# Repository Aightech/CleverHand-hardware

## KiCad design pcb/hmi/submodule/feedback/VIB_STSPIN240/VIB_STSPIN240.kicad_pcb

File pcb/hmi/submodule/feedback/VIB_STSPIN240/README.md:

# Vibrotactile STSPIN240 Module
This module is a vibrotactile module that embeds the STSPIN240 motor driver. It is responsible for generating the vibrotactile signals that will be sent to the vibrotactile actuators.

## Electrical Schematic

## PCB Layout
|top view|side view|
|---|---|
|  |  |

## 3D Model
[VIB_STSPIN240_3D](plots/VIB_STSPIN240_pcb.stl)

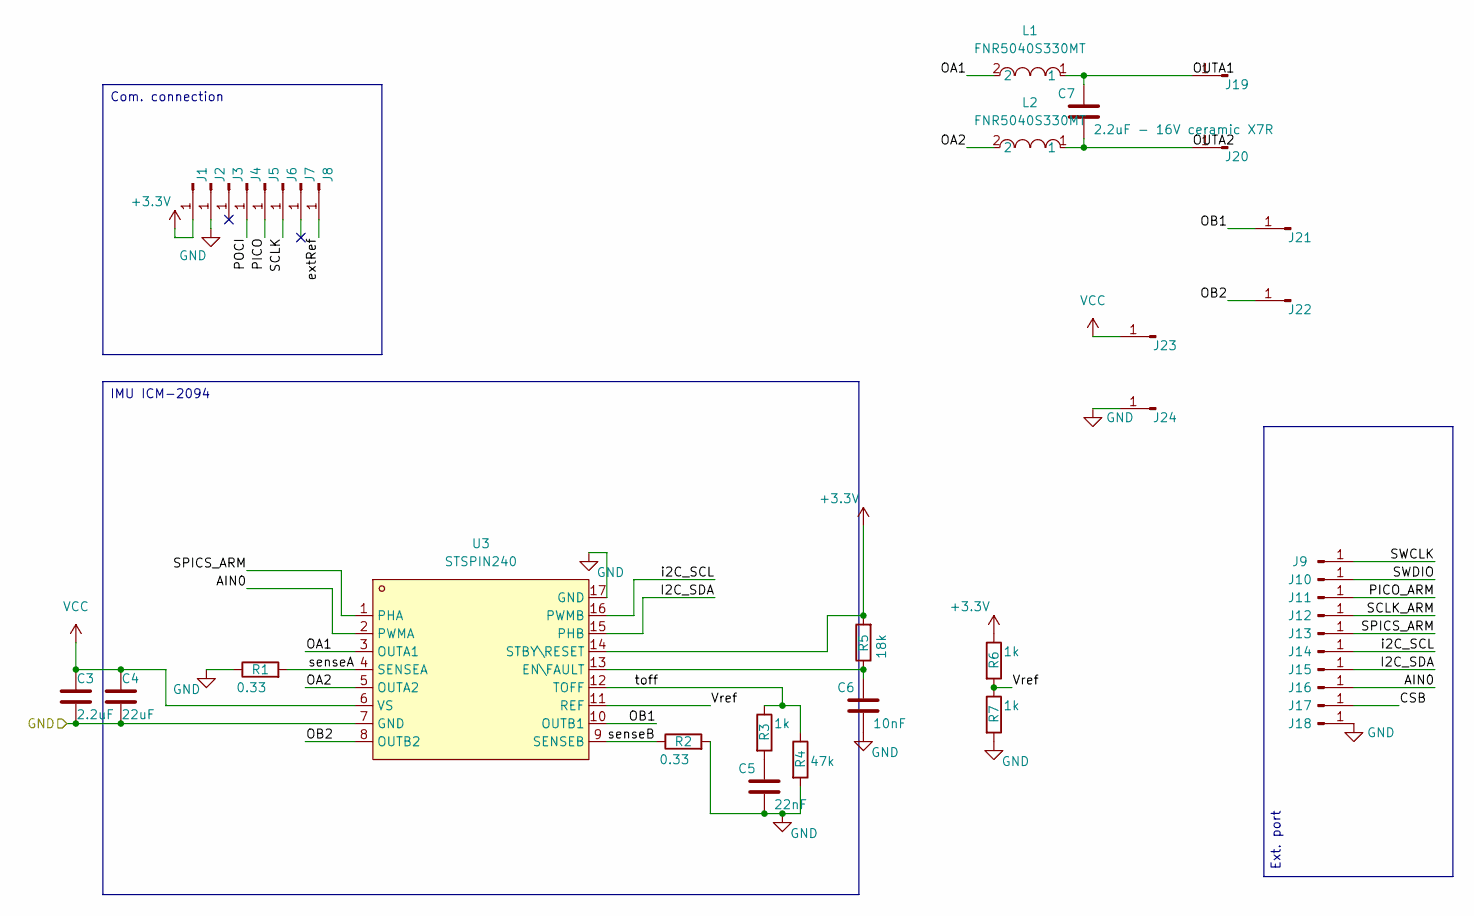
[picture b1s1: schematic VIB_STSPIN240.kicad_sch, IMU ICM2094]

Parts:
C3: 2.2uF; C_0402_1005Metric; LCSC C12530
C4: 22uF; C_0402_1005Metric; LCSC C1532
C5: 22nF; C_0402_1005Metric; LCSC C1532
C6: 10nF; C_0402_1005Metric; LCSC C15195
C7: 2.2uF - 16V ceramic X7R; C_0603_1608Metric; LCSC C23630
J1, J2, J3, J4, J5, J6, J7, J8, J9, J10, J11, J12, J13, J14, J15, J16, J17, J18, J19, J20, J21, J22, J23, J24: Conn_01x01_Pin; PinHeader_1x01_P1.27mm_Vertical
L1, L2: FNR5040S330MT; IND-SMD_L5.0-W5.0_FNR50XXS; LCSC Part C167973
R1: 0.33; R_1206_3216Metric; LCSC C25337
R2: 0.33; R_1206_3216Metric
R3, R6, R7: 1k; R_0402_1005Metric; LCSC C11702
R4: 47k; R_0402_1005Metric; LCSC C25792
R5: 18k; R_0402_1005Metric; LCSC C25762
U3: STSPIN240; QFN-16_L3.0-W3.0-P0.50-BL-EP1.7; LCSC Part C962258

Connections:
+3.3V: J1.1, R5.2, R6.1, U3.14 (STBY\RESET)
/AIN0: J16.1, U3.2 (PWMA)
/CSB: J17.1
/I2C_SDA: J15.1, U3.15 (PHB)
/OA1: L1.2, U3.3 (OUTA1)
/OA2: L2.2, U3.5 (OUTA2)
/OB1: J21.1, U3.10 (OUTB1)
/OB2: J22.1, U3.8 (OUTB2)
/OUTA1: C7.1, J19.1, L1.1
/OUTA2: C7.2, J20.1, L2.1
/PICO: J5.1
/PICO_ARM: J11.1
/POCI: J4.1
/SCLK: J6.1
/SCLK_ARM: J12.1
/SPICS_ARM: J13.1, U3.1 (PHA)
/SWCLK: J9.1
/SWDIO: J10.1
/Vref: R6.2, R7.1, U3.11 (REF)
/extRef: J8.1
/i2C_SCL: J14.1, U3.16 (PWMB)
/senseA: R1.2, U3.4 (SENSEA)
/senseB: R2.1, U3.9 (SENSEB)
/toff: R3.1, R4.1, U3.12 (TOFF)
GND: C3.2, C4.2, C5.2, C6.2, J2.1, J18.1, J24.1, R1.1, R2.2, R4.2, R7.2, U3.7 (GND), U3.17 (GND)
unnamed: C5.1, R3.2
unnamed: C6.1, R5.1, U3.13 (EN\FAULT)
VCC: C3.1, C4.1, J23.1, U3.6 (VS)

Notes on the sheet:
Com. connection
Ext. port
IMU ICM-2094

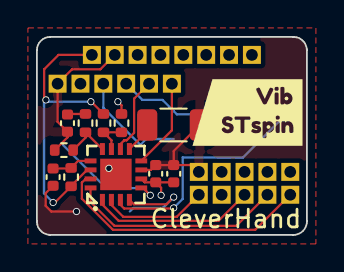
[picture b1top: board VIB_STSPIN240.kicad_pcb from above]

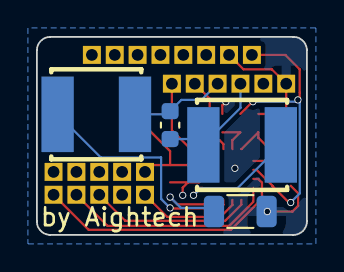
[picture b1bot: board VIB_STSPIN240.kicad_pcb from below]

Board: 4 copper layers, 15.0 x 11.0 mm, 40 parts (4 on the bottom side), 19 nets.

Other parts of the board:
kibuzzard-66089A17: G***; kibuzzard-66089A17

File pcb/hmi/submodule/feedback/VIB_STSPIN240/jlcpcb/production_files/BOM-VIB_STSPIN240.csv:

Comment,Designator,Footprint,LCSC,Quantity
0.33,"R1,R2",R_1206_3216Metric,C25337,2
10nF,C6,C_0402_1005Metric,C15195,1
18k,R5,R_0402_1005Metric,C25762,1
1k,"R3,R6,R7",R_0402_1005Metric,C11702,3
2.2uF,C3,C_0402_1005Metric,C12530,1
2.2uF - 16V ceramic X7R,C7,C_0603_1608Metric,C23630,1
22nF,C5,C_0402_1005Metric,C1532,1
22uF,C4,C_0402_1005Metric,C105226,1
47k,R4,R_0402_1005Metric,C25792,1
FNR5040S330MT,"L1,L2",IND-SMD_L5.0-W5.0_FNR50XXS,C167973,2
STSPIN240,U3,QFN-16_L3.0-W3.0-P0.50-BL-EP1.7,C962258,1

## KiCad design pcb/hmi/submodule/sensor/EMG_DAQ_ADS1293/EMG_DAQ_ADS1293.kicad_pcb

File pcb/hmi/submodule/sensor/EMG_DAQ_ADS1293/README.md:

# EMG ADS1293 Module
This module is a data acquisition module that embeds the ADS1293 analog front-end. It is responsible for acquiring the EMG signals from the electrodes.

## Electrical Schematic

## PCB Layout
|top view|side view|
|---|---|
 |  |  |

## 3D Model
[EMG_DAQ_ADS1293_3D](plots/EMG_DAQ_ADS1293_pcb.stl)

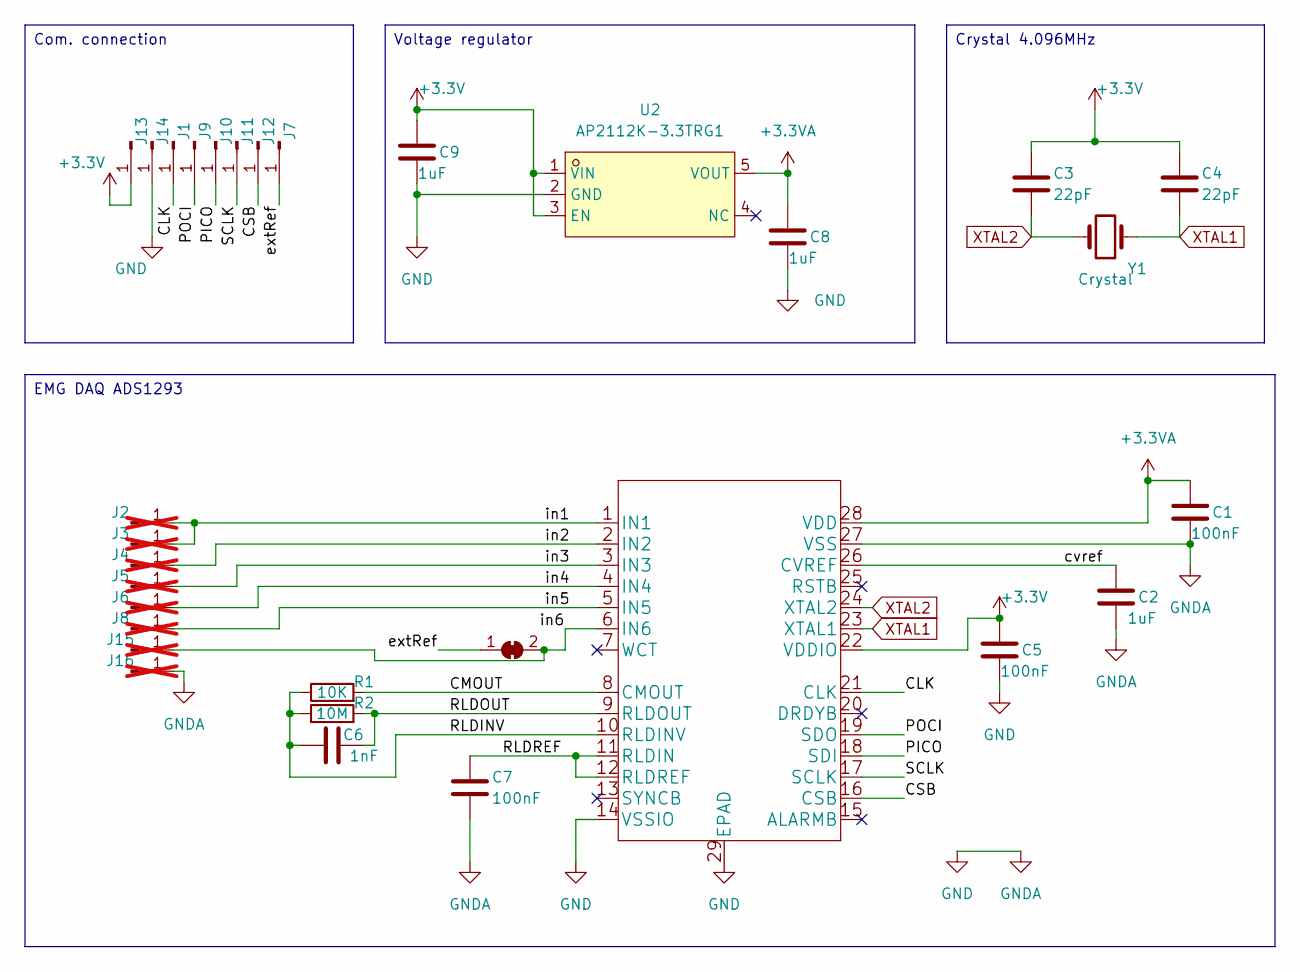
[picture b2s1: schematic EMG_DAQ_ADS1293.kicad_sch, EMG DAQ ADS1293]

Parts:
C1, C5, C7: 100nF; C_0402_1005Metric
C2, C8, C9: 1uF; C_0402_1005Metric
C3, C4: 22pF; C_0402_1005Metric; LCSC C1555
C6: 1nF; C_0402_1005Metric; LCSC C1523
J1, J7, J9, J10, J11, J12, J13, J14: Conn_01x01_Pin; PinHeader_1x01_P1.27mm_Vertical
J2, J3, J4, J5, J6, J8, J15, J16: Conn_01x01_Pin; PinHeader_1x01_P1.27mm_Vertical; not fitted
JP2: SolderJumper_2_Bridged; SolderJumper-2_P1.3mm_Bridged2Bar_RoundedPad1.0x1.5mm
R1: 10K; C_0402_1005Metric; LCSC C25744
R2: 10M; C_0402_1005Metric; LCSC C26082
U1: ADS1293CISQE-NOPB; ADS1293CISQE; LCSC C181260
U2: AP2112K-3.3TRG1; SOT-25-5_L2.9-W1.6-P0.95-LS2.8-BL; LCSC Part C51118
Y1: Crystal; Crystal_SMD_HC49-SD; LCSC C74858

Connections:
+3.3V: C3.1, C4.1, C5.1, C9.1, J13.1, U1.22 (VDDIO), U2.1 (VIN), U2.3 (EN)
+3.3VA: C1.1, C8.1, U1.28 (VDD), U2.5 (VOUT)
/CLK: J1.1, U1.21 (CLK)
/CMOUT: R1.2, U1.8 (CMOUT)
/CSB: J12.1, U1.16 (CSB)
/PICO: J10.1, U1.18 (SDI)
/POCI: J9.1, U1.19 (SDO)
/RLDINV: C6.1, R1.1, R2.1, U1.10 (RLDINV)
/RLDOUT: C6.2, R2.2, U1.9 (RLDOUT)
/RLDREF: C7.1, U1.11 (RLDIN), U1.12 (RLDREF)
/SCLK: J11.1, U1.17 (SCLK)
/cvref: C2.1, U1.26 (CVREF)
/extRef: J7.1, JP2.1 (A)
/in1: J2.1, J3.1, U1.1 (IN1)
/in2: J4.1, U1.2 (IN2)
/in3: J5.1, U1.3 (IN3)
/in4: J6.1, U1.4 (IN4)
/in5: J8.1, U1.5 (IN5)
/in6: J15.1, JP2.2 (B), U1.6 (IN6)
GND: C1.2, C2.2, C5.2, C7.2, C8.2, C9.2, J14.1, J16.1, U1.14 (VSSIO), U1.27 (VSS), U1.29 (EPAD), U2.2 (GND)
XTAL1: C4.2, U1.23 (XTAL1), Y1.1
XTAL2: C3.2, U1.24 (XTAL2), Y1.2

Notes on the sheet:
Com. connection
Crystal 4.096MHz
Voltage regulator
EMG DAQ ADS1293

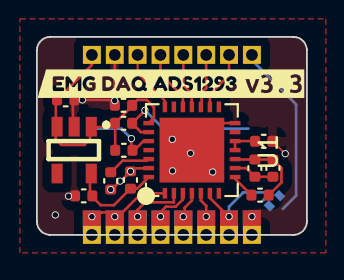
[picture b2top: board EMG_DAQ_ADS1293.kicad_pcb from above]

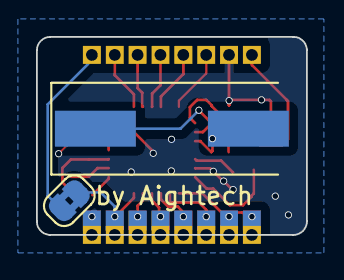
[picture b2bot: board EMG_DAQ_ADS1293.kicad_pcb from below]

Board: 4 copper layers, 15.0 x 11.0 mm, 33 parts (2 on the bottom side), 22 nets.

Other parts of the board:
kibuzzard-658D7E24: G***; kibuzzard-658D7E24
kibuzzard-69472C09: G***; kibuzzard-69472C09

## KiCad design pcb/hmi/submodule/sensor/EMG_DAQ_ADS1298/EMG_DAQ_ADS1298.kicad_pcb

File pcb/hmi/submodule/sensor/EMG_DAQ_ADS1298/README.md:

# EMG ADS1298 Module
This module is a data acquisition module that embeds the ADS1298 analog front-end. It is responsible for acquiring the EMG signals from the electrodes.

## Electrical Schematic

## PCB Layout
|top view|side view|
|---|---|
 |  |  |

## 3D Model
[EMG_DAQ_ADS1298_3D](plots/EMG_DAQ_ADS1298_pcb.stl)

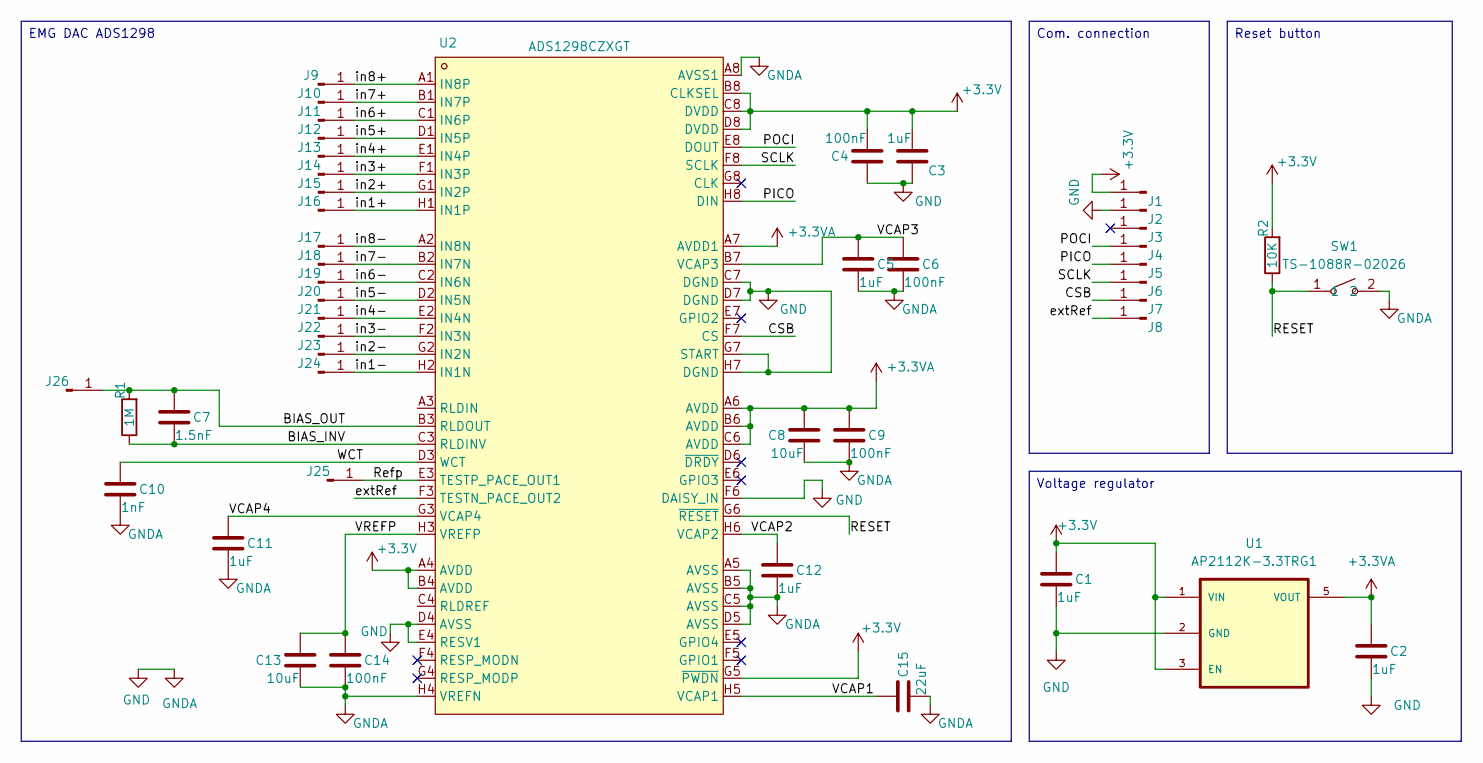
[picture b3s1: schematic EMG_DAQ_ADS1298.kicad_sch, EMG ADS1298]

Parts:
C1, C2, C3, C5, C11, C12: 1uF; C_0402_1005Metric
C4, C6, C9, C14: 100nF; C_0402_1005Metric
C7: 1.5nF; C_0402_1005Metric
C8, C13: 10uF; C_0402_1005Metric
C10: 1nF; C_0402_1005Metric
C15: 22uF; C_0402_1005Metric
J1, J2, J3, J4, J5, J6, J7, J8, J25, J26: Conn_01x01_Pin; PinHeader_1x01_P1.27mm_Vertical
J9, J10, J11, J12, J13, J14, J15, J16, J17, J18, J19, J20, J21, J22, J23, J24: Conn_01x01_Pin; SolderWirePad_1x01_SMD_1x2mm
R1: 1M; C_0402_1005Metric
R2: 10K; C_0402_1005Metric
SW1: TS-1088R-02026; SW-SMD_L3.9-W3.0-P4.45; LCSC Part C455280
U1: AP2112K-3.3TRG1; SOT95P285X140-5N; PARTREV 2-2
U2: ADS1298CZXGT; NFBGA-64_L8.0-W8.0-R8-C8-P0.80-TL; LCSC Part C882732

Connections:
+3.3V: C1.1, C3.2, C4.2, J1.1, R2.2, U1.1 (VIN), U1.3 (EN), U2.A4 (AVDD), U2.B4 (AVDD), U2.B8 (CLKSEL), U2.C8 (DVDD), U2.D8 (DVDD), U2.G5 (~PWDN)
+3.3VA: C2.1, C8.1, C9.1, U1.5 (VOUT), U2.A6 (AVDD), U2.A7 (AVDD1), U2.B6 (AVDD), U2.C6 (AVDD)
/BIAS_INV: C7.2, R1.1, U2.C3 (RLDINV)
/BIAS_OUT: C7.1, J26.1, R1.2, U2.B3 (RLDOUT)
/CSB: J7.1, U2.F7 (CS)
/PICO: J5.1, U2.H8 (DIN)
/POCI: J4.1, U2.E8 (DOUT)
/RESET: R2.1, SW1.1, U2.G6 (~RESET)
/Refp: J25.1, U2.E3 (TESTP_PACE_OUT1)
/SCLK: J6.1, U2.F8 (SCLK)
/VCAP1: C15.1, U2.H5 (VCAP1)
/VCAP2: C12.1, U2.H6 (VCAP2)
/VCAP3: C5.1, C6.1, U2.B7 (VCAP3)
/VCAP4: C11.1, U2.G3 (VCAP4)
/VREFP: C13.1, C14.1, U2.H3 (VREFP)
/WCT: C10.1, U2.D3 (WCT)
/extRef: J8.1, U2.F3 (TESTN_PACE_OUT2)
/in1+: J16.1, U2.H1 (IN1P)
/in1-: J24.1, U2.H2 (IN1N)
/in2+: J15.1, U2.G1 (IN2P)
/in2-: J23.1, U2.G2 (IN2N)
/in3+: J14.1, U2.F1 (IN3P)
/in3-: J22.1, U2.F2 (IN3N)
/in4+: J13.1, U2.E1 (IN4P)
/in4-: J21.1, U2.E2 (IN4N)
/in5+: J12.1, U2.D1 (IN5P)
/in5-: J20.1, U2.D2 (IN5N)
/in6+: J11.1, U2.C1 (IN6P)
/in6-: J19.1, U2.C2 (IN6N)
/in7+: J10.1, U2.B1 (IN7P)
/in7-: J18.1, U2.B2 (IN7N)
/in8+: J9.1, U2.A1 (IN8P)
/in8-: J17.1, U2.A2 (IN8N)
GND: C1.2, C2.2, C3.1, C4.1, C5.2, C6.2, C8.2, C9.2, C10.2, C11.2, C12.2, C13.2, C14.2, C15.2, J2.1, SW1.2, U1.2 (GND), U2.A5 (AVSS), U2.A8 (AVSS1), U2.B5 (AVSS), U2.C5 (AVSS), U2.C7 (DGND), U2.D4 (AVSS), U2.D5 (AVSS), U2.D7 (DGND), U2.E4 (RESV1), U2.F6 (DAISY_IN), U2.G7 (START), U2.H4 (VREFN), U2.H7 (DGND)

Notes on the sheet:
EMG DAC ADS1298
Voltage regulator
Com. connection
Reset button

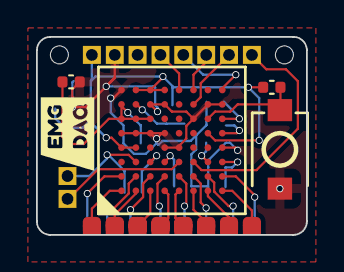
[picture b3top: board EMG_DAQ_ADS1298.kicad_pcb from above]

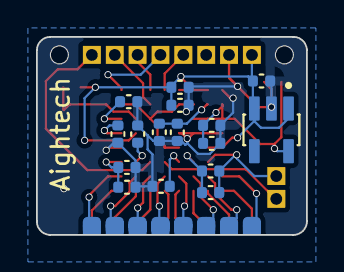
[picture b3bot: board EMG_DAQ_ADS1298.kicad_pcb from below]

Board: 4 copper layers, 15.0 x 11.0 mm, 47 parts (24 on the bottom side), 34 nets.

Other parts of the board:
kibuzzard-6569F40D: G***; kibuzzard-6569F40D

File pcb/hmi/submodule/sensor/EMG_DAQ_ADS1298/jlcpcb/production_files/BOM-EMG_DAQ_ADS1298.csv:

Comment,Designator,Footprint,LCSC,Quantity
ADS1298CZXGT,U2,NFBGA-64_L8.0-W8.0-R8-C8-P0.80-TL,C882732,1
TS-1088R-02026,SW1,SW-SMD_L3.9-W3.0-P4.45,C455280,1
Conn_01x01_Pin,J1,PinHeader_1x01_P1.27mm_Vertical,,1
Conn_01x01_Pin,J5,PinHeader_1x01_P1.27mm_Vertical,,1
Conn_01x01_Pin,J4,PinHeader_1x01_P1.27mm_Vertical,,1
10K,R2,C_0402_1005Metric,,1
Conn_01x01_Pin,J8,PinHeader_1x01_P1.27mm_Vertical,,1
Conn_01x01_Pin,J7,PinHeader_1x01_P1.27mm_Vertical,,1
Conn_01x01_Pin,J25,PinHeader_1x01_P1.27mm_Vertical,,1
Conn_01x01_Pin,J26,PinHeader_1x01_P1.27mm_Vertical,,1
Conn_01x01_Pin,J2,PinHeader_1x01_P1.27mm_Vertical,,1
Conn_01x01_Pin,J6,PinHeader_1x01_P1.27mm_Vertical,,1
Conn_01x01_Pin,J3,PinHeader_1x01_P1.27mm_Vertical,,1
1uF,C2,C_0402_1005Metric,,1
1uF,C11,C_0402_1005Metric,,1
10uF,C13,C_0402_1005Metric,,1
100nF,C14,C_0402_1005Metric,,1
1uF,C1,C_0402_1005Metric,,1
1uF,C3,C_0402_1005Metric,,1
1nF,C10,C_0402_1005Metric,,1
AP2112K-3.3TRG1,U1,SOT95P285X140-5N,,1
1uF,C5,C_0402_1005Metric,,1
1.5nF,C7,C_0402_1005Metric,,1
1M,R1,C_0402_1005Metric,,1
100nF,C4,C_0402_1005Metric,,1
10uF,C8,C_0402_1005Metric,,1
22uF,C15,C_0402_1005Metric,,1
100nF,C9,C_0402_1005Metric,,1
1uF,C12,C_0402_1005Metric,,1
100nF,C6,C_0402_1005Metric,,1

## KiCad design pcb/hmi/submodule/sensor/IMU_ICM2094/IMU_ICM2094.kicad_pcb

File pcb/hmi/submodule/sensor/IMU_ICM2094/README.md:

# IMU ICM2094 Module
This module is an Inertial Measurement Unit (IMU) that embeds the ICM2094 sensor. It is responsible for acquiring the acceleration, angular velocity and magnetic field signals.

## Electrical Schematic

## PCB Layout
|top view|side view|
|---|---|
 |  |  |

## 3D Model
[IMU_ICM2094_3D](plots/IMU_ICM2094_pcb.stl)

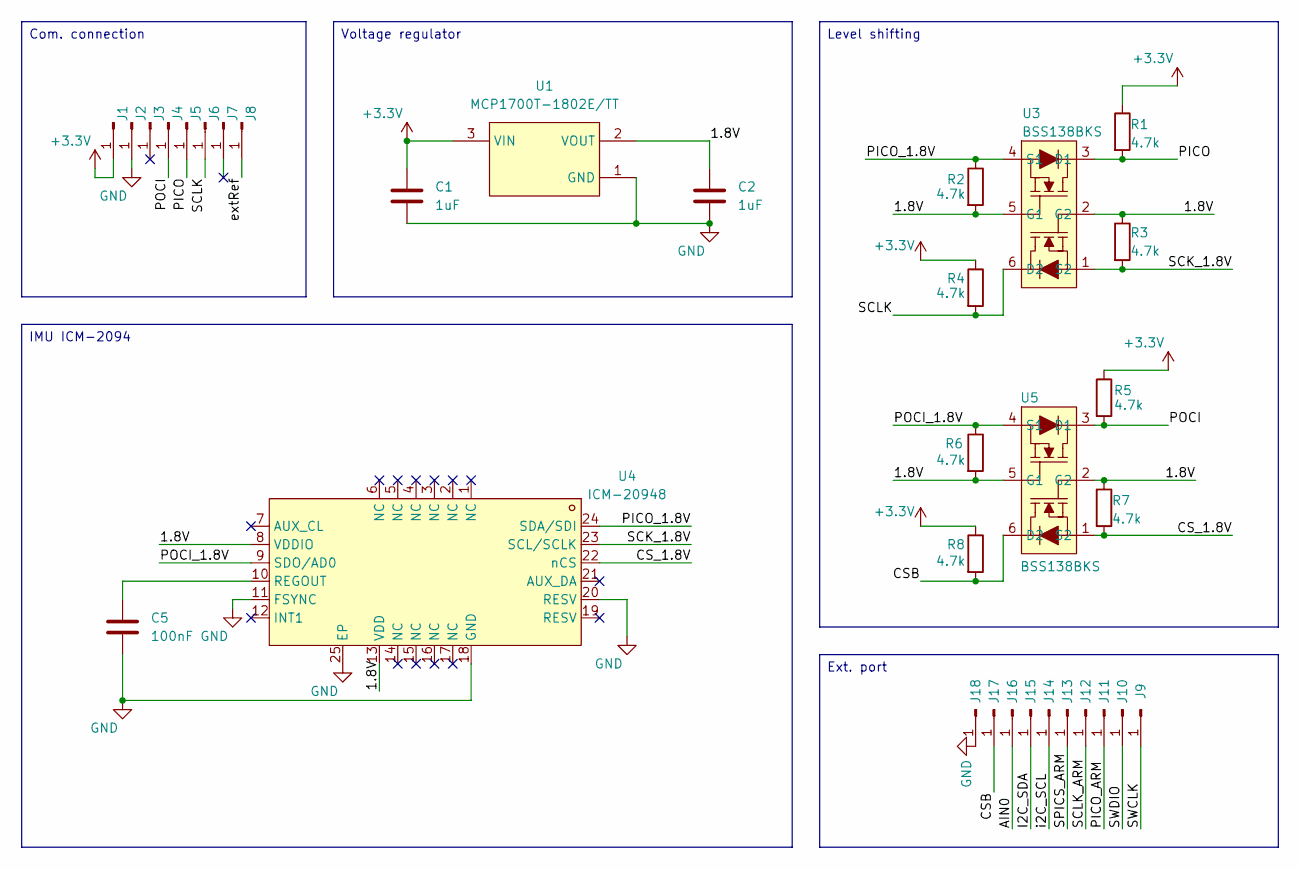
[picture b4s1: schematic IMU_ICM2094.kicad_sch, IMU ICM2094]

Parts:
C1, C2: 1uF; C_0402_1005Metric
C5: 100nF; C_0402_1005Metric
J1, J2, J3, J4, J5, J6, J7, J8, J9, J10, J11, J12, J13, J14, J15, J16, J17, J18: Conn_01x01_Pin; PinHeader_1x01_P1.27mm_Vertical
R1, R2, R3, R4, R5, R6, R7, R8: 4.7k; R_0402_1005Metric
U1: MCP1700T-1802E/TT; SOT-23-3_L2.9-W1.3-P1.90-LS2.4-BR; LCSC Part C150796
U3, U5: BSS138BKS; SOT-363_L2.1-W1.3-P0.65-LS2.3-BL; LCSC Part C5224290
U4: ICM-20948; QFN-24-1EP_3x3mm_P0.4mm_EP1.75x1.6mm; LCSC Part C726001

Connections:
+3.3V: C1.1, J1.1, R1.1, R4.1, R5.1, R8.1, U1.3 (VIN)
/1.8V: C2.1, R2.2, R3.1, R6.2, R7.1, U1.2 (VOUT), U3.2 (G2), U3.5 (G1), U4.8 (VDDIO), U4.13 (VDD), U5.2 (G2), U5.5 (G1)
/AIN0: J16.1
/CSB: J17.1, R8.2, U5.6 (D2)
/CS_1.8V: R7.2, U4.22 (nCS), U5.1 (S2)
/I2C_SDA: J15.1
/IO1_out: J9.1
/PICO: J5.1, R1.2, U3.3 (D1)
/PICO_1.8V: R2.1, U3.4 (S1), U4.24 (SDA/SDI)
/PICO_ARM: J11.1
/POCI: J4.1, R5.2, U5.3 (D1)
/POCI_1.8V: R6.1, U4.9 (SDO/AD0), U5.4 (S1)
/SCK_1.8V: R3.2, U3.1 (S2), U4.23 (SCL/SCLK)
/SCLK: J6.1, R4.2, U3.6 (D2)
/SCLK_ARM: J12.1
/SPICS_ARM: J13.1
/SWDIO/POCI_ARM: J10.1
/extRef: J8.1
/i2C_SCL: J14.1
GND: C1.2, C2.2, C5.2, J2.1, J18.1, U1.1 (GND), U4.11 (FSYNC), U4.18 (GND), U4.20 (RESV), U4.25 (EP)
unnamed: C5.1, U4.10 (REGOUT)

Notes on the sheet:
Com. connection
Ext. port
Level shifting
Voltage regulator
IMU ICM-2094

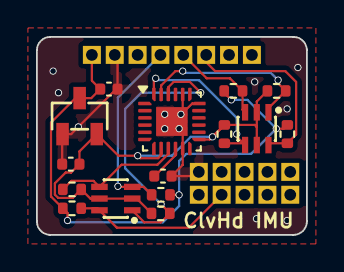
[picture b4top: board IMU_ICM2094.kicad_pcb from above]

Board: 4 copper layers, 15.0 x 11.0 mm, 34 parts (1 on the bottom side), 12 nets.

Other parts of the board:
kibuzzard-66093797: G***; kibuzzard-66093797

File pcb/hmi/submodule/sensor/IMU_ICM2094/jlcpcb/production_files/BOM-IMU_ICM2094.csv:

Comment,Designator,Footprint,LCSC,Quantity
100nF,C5,C_0402_1005Metric,C1525,1
1uF,"C1,C2",C_0402_1005Metric,C52923,2
4.7k,"R1,R2,R3,R4,R5,R6,R7,R8",R_0402_1005Metric,C25900,8
BSS138BKS,"U3,U5",SOT-363_L2.1-W1.3-P0.65-LS2.3-BL,C5224290,2
ICM-20948,U4,QFN-24-1EP_3x3mm_P0.4mm_EP1.75x1.6mm,C726001,1
MCP1700T-1802E/TT,U1,SOT-23-3_L2.9-W1.3-P1.90-LS2.4-BR,C150796,1

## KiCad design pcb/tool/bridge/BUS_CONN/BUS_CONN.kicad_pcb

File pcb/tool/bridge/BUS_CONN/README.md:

# Bus Connection
This module is a passive bridge to easily access the cleverhand bus tracks.

## Electrical Schematic

## PCB Layout
| top | bottom |
| --- | --- |
| |  |

## 3D Model
[BUS_CONN_3D](plots/BUS_CONN_pcb.stl)

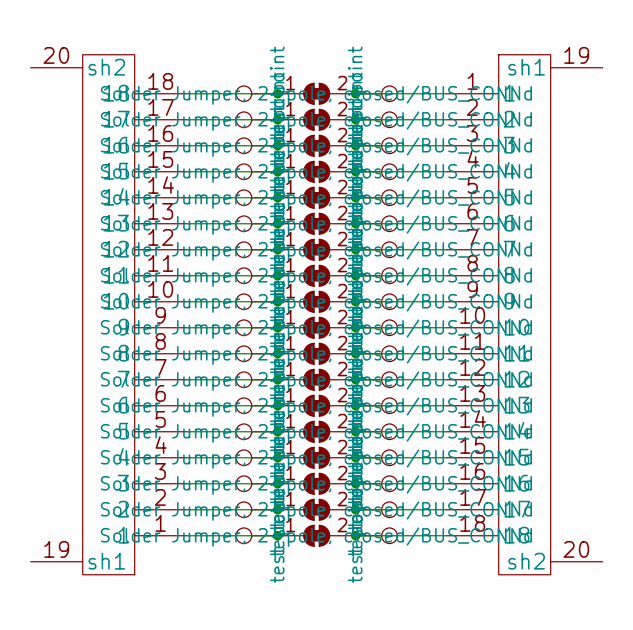
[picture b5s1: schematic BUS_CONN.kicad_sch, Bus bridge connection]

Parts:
J1, J2: XF2J-1824-12A; LCSC C397324
JP1, JP2, JP3, JP4, JP5, JP6, JP7, JP8, JP9, JP10, JP11, JP12, JP13, JP14, JP15, JP16, JP17, JP18: SolderJumper_2_Bridged; SolderJumper-2_P1.3mm_Bridged_RoundedPad1.0x1.5mm
TP1, TP2, TP3, TP4, TP5, TP6, TP7, TP8, TP9, TP10, TP11, TP12, TP13, TP14, TP15, TP16, TP17, TP18, TP19, TP20, TP21, TP22, TP23, TP24, TP25, TP26, TP27, TP28, TP29, TP30, TP31, TP32, TP33, TP34, TP35, TP36: TestPoint; PinHeader_1x01_P2.54mm_Vertical

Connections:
unnamed: J1.18, JP1.1 (A), TP1.1
unnamed: J2.1, JP1.2 (B), TP19.1
unnamed: J1.17, JP2.1 (A), TP2.1
unnamed: J2.2, JP2.2 (B), TP20.1
unnamed: J1.16, JP3.1 (A), TP3.1
unnamed: J2.3, JP3.2 (B), TP21.1
unnamed: J1.15, JP4.1 (A), TP4.1
unnamed: J2.4, JP4.2 (B), TP22.1
unnamed: J1.14, JP5.1 (A), TP5.1
unnamed: J2.5, JP5.2 (B), TP23.1
unnamed: J1.13, JP6.1 (A), TP6.1
unnamed: J2.6, JP6.2 (B), TP24.1
unnamed: J1.12, JP7.1 (A), TP7.1
unnamed: J2.7, JP7.2 (B), TP25.1
unnamed: J1.11, JP8.1 (A), TP8.1
unnamed: J2.8, JP8.2 (B), TP26.1
unnamed: J1.10, JP9.1 (A), TP9.1
unnamed: J2.9, JP9.2 (B), TP27.1
unnamed: J1.9, JP10.1 (A), TP10.1
unnamed: J2.10, JP10.2 (B), TP28.1
unnamed: J1.8, JP11.1 (A), TP11.1
unnamed: J2.11, JP11.2 (B), TP29.1
unnamed: J1.7, JP12.1 (A), TP12.1
unnamed: J2.12, JP12.2 (B), TP30.1
unnamed: J1.6, JP13.1 (A), TP13.1
unnamed: J2.13, JP13.2 (B), TP31.1
unnamed: J1.5, JP14.1 (A), TP14.1
unnamed: J2.14, JP14.2 (B), TP32.1
unnamed: J1.4, JP15.1 (A), TP15.1
unnamed: J2.15, JP15.2 (B), TP33.1
unnamed: J1.3, JP16.1 (A), TP16.1
unnamed: J2.16, JP16.2 (B), TP34.1
unnamed: J1.2, JP17.1 (A), TP17.1
unnamed: J2.17, JP17.2 (B), TP35.1
unnamed: J1.1, JP18.1 (A), TP18.1
unnamed: J2.18, JP18.2 (B), TP36.1

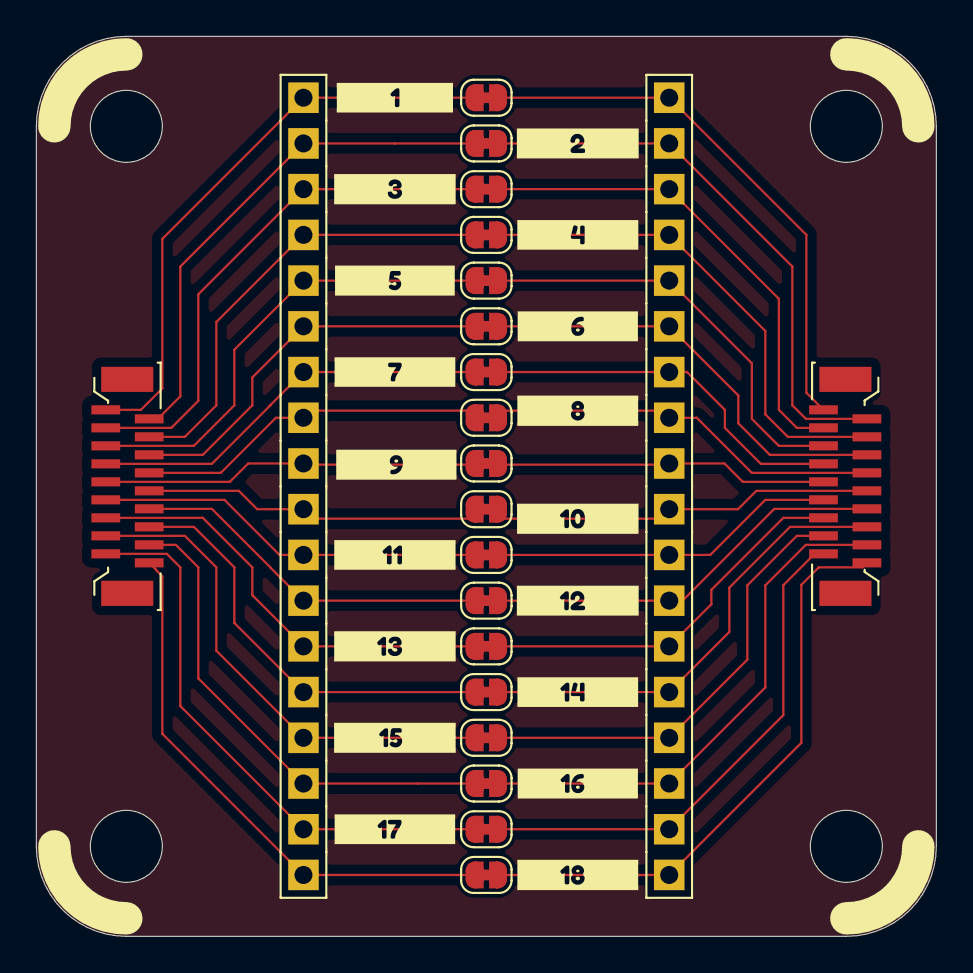
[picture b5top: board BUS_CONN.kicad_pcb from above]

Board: 4 copper layers, 50.0 x 50.0 mm, 74 parts (0 on the bottom side), 36 nets.

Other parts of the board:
kibuzzard-63B56CBF: G***; kibuzzard-63B56CBF
kibuzzard-63B56D3C: G***; kibuzzard-63B56D3C
kibuzzard-63B56D06: G***; kibuzzard-63B56D06
kibuzzard-63B56D6D: G***; kibuzzard-63B56D6D
kibuzzard-63B56D79: G***; kibuzzard-63B56D79
kibuzzard-63B56EBC: G***; kibuzzard-63B56EBC
kibuzzard-63B56EF1: G***; kibuzzard-63B56EF1
kibuzzard-63B56F8D: G***; kibuzzard-63B56F8D
kibuzzard-63B56F28: G***; kibuzzard-63B56F28
kibuzzard-63B56F37: G***; kibuzzard-63B56F37
kibuzzard-63B56F80: G***; kibuzzard-63B56F80
kibuzzard-63B56F84: G***; kibuzzard-63B56F84
kibuzzard-63B56F93: G***; kibuzzard-63B56F93
kibuzzard-63B56FB5: G***; kibuzzard-63B56FB5
kibuzzard-63B56FC4: G***; kibuzzard-63B56FC4
kibuzzard-63B56FCC: G***; kibuzzard-63B56FCC
kibuzzard-63B56FD6: G***; kibuzzard-63B56FD6
kibuzzard-63B56FE1: G***; kibuzzard-63B56FE1

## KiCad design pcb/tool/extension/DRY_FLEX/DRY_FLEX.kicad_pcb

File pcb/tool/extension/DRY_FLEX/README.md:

# Flex Interface Module
This module extends the electrodes module. It a flexible PCB that connects the electrodes module and offers a flexible interface to the user.

## Electrical Schematic

## PCB Layout
|top view|side view|
|---|---|
|||

## 3D Model
[DRY_FLEX_3D](plots/DRY_FLEX_pcb.stl)

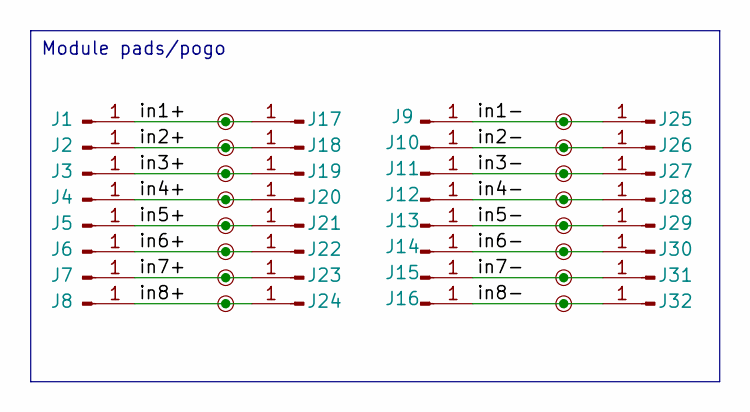
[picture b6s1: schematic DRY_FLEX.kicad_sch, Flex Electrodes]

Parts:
J1, J2, J3, J4, J5, J6, J7, J8, J9, J10, J11, J12, J13, J14, J15, J16, J17, J18, J19, J20, J21, J22, J23, J24, J25, J26, J27, J28, J29, J30, J31, J32: Conn_01x01_Pin; Pin_D1.2mm_pogo
TP1, TP2, TP3, TP4, TP5, TP6, TP7, TP8, TP9, TP10, TP11, TP12, TP13, TP14, TP15, TP16: TestPoint; SolderWirePad_1x01_SMD_1x2mm

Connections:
/in1+: J1.1, J17.1, TP9.1
/in1-: J9.1, J25.1, TP1.1
/in2+: J2.1, J18.1, TP10.1
/in2-: J10.1, J26.1, TP2.1
/in3+: J3.1, J19.1, TP11.1
/in3-: J11.1, J27.1, TP3.1
/in4+: J4.1, J20.1, TP12.1
/in4-: J12.1, J28.1, TP4.1
/in5+: J5.1, J21.1, TP13.1
/in5-: J13.1, J29.1, TP5.1
/in6+: J6.1, J22.1, TP14.1
/in6-: J14.1, J30.1, TP6.1
/in7+: J7.1, J23.1, TP15.1
/in7-: J15.1, J31.1, TP7.1
/in8+: J8.1, J24.1, TP16.1
/in8-: J16.1, J32.1, TP8.1

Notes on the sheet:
Module pads/pogo

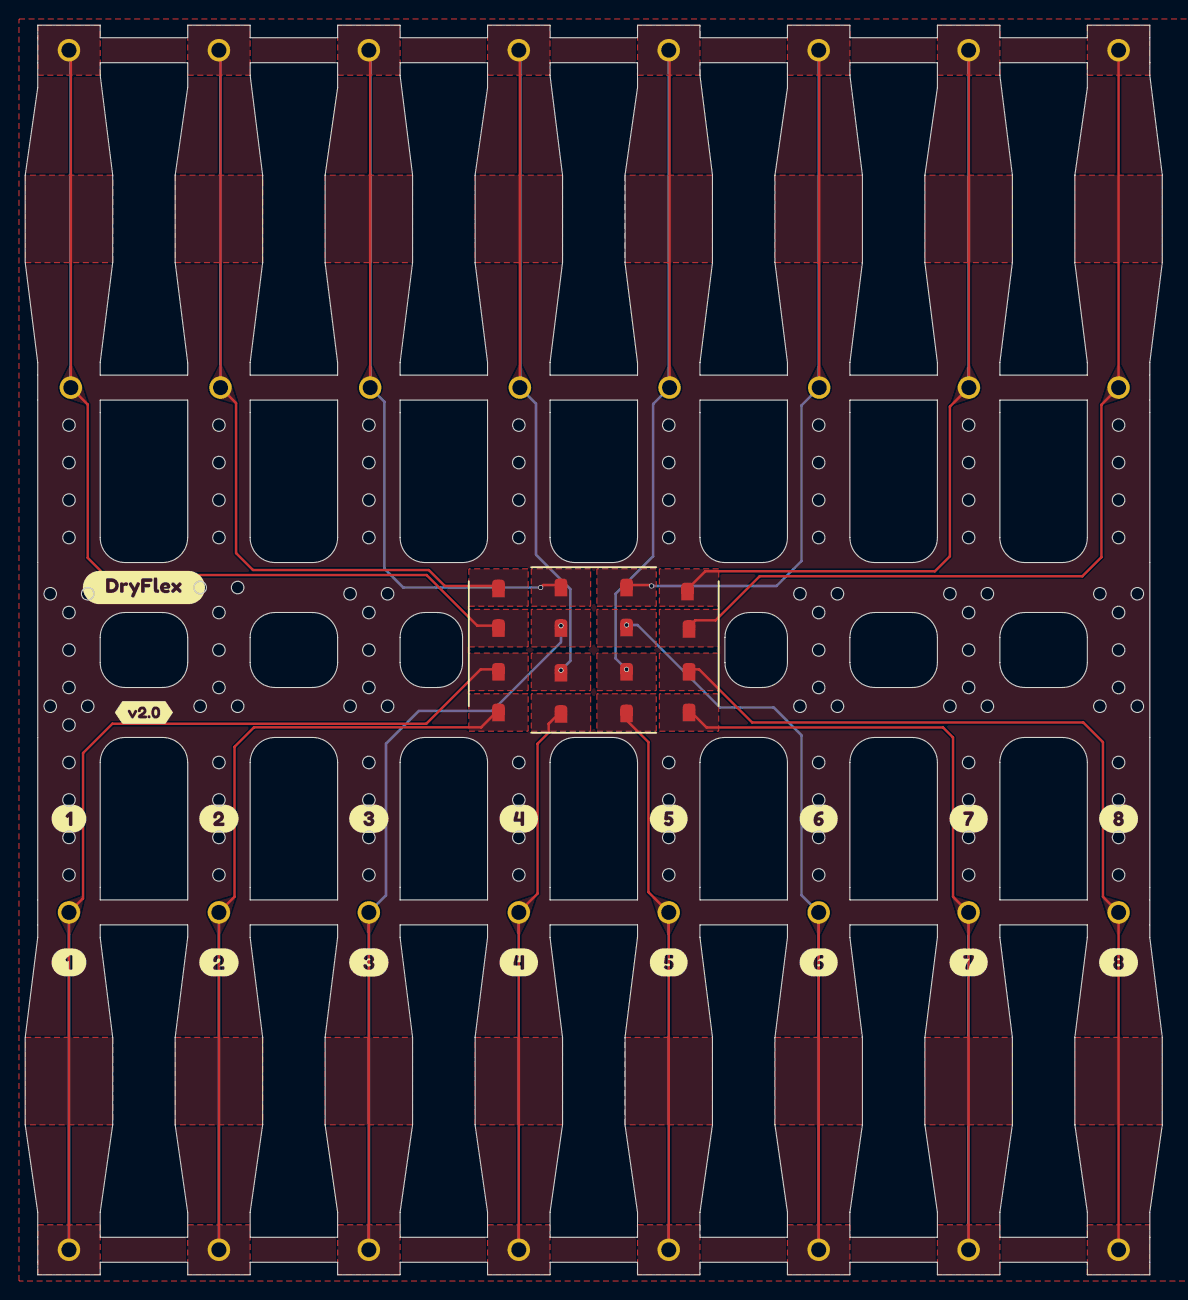
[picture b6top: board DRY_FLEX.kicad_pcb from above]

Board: 2 copper layers, 91.0 x 100.0 mm, 67 parts (1 on the bottom side), 16 nets.

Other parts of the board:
kibuzzard-658EC94F, kibuzzard-658EC94F#2: G***; kibuzzard-658EC94F
kibuzzard-658EC95B, kibuzzard-658EC95B#2: G***; kibuzzard-658EC95B
kibuzzard-658EC936, kibuzzard-658EC936#2: G***; kibuzzard-658EC936
kibuzzard-658EC955, kibuzzard-658EC955#2: G***; kibuzzard-658EC955
kibuzzard-658EC960, kibuzzard-658EC960#2: G***; kibuzzard-658EC960
kibuzzard-66085B0B, kibuzzard-66085B0B#2: G***; kibuzzard-66085B0B
kibuzzard-66085B03, kibuzzard-66085B03#2: G***; kibuzzard-66085B03
kibuzzard-66085B10, kibuzzard-66085B10#2: G***; kibuzzard-66085B10
kibuzzard-66085C02: G***; kibuzzard-66085C02
kibuzzard-660866D6: G***; kibuzzard-660866D6
kibuzzard-6608669B: G***; kibuzzard-6608669B

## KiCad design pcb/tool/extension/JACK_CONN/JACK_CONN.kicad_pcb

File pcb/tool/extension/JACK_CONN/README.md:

# Jack Connection
 This extension board let you connect a hmi module (with a 4x4 dry interface) to jack connector. 

## Electrical Schematic

## PCB Layout
|top view|side view|
|---|---|
 |  |  |

## 3D Model
[JACK_CONN_3D](plots/JACK_CONN_pcb.stl)

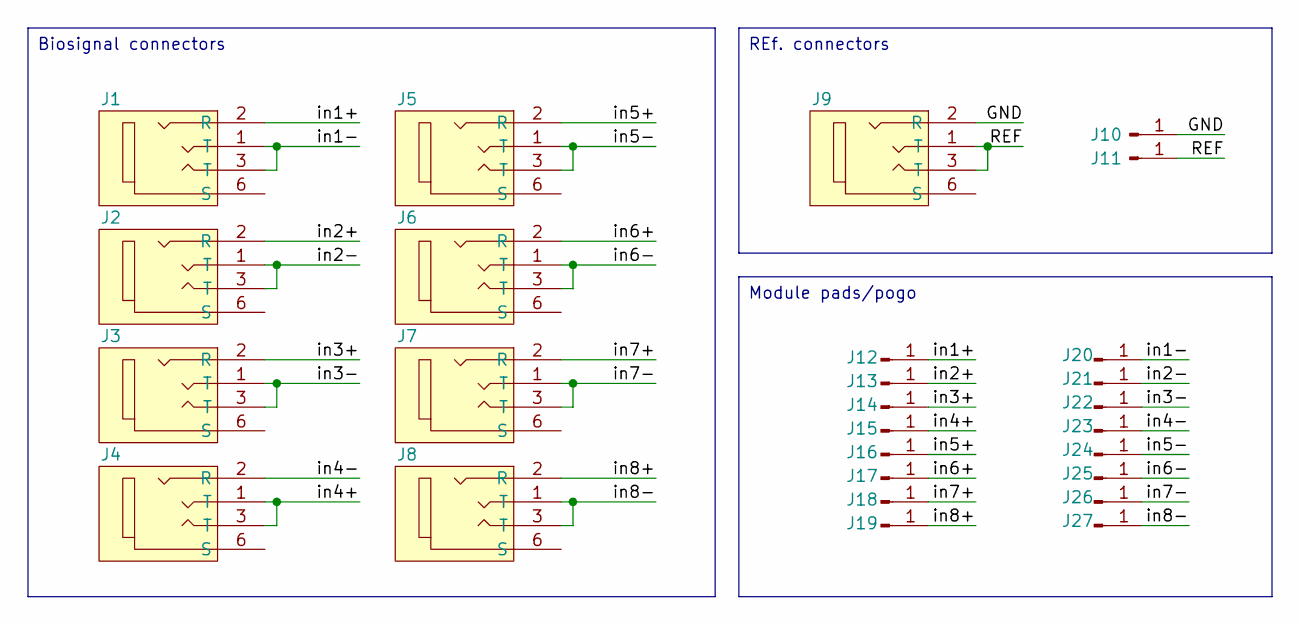
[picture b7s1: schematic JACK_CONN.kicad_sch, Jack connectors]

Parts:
J1, J2, J3, J4, J5, J6, J7, J8, J9: jack2.5_PJ-210B; Jack_Socket_PJ-210B
J10, J11: Conn_01x01_Pin; PinHeader_1x01_P2.54mm_Vertical
J12, J13, J14, J15, J16, J17, J18, J19, J20, J21, J22, J23, J24, J25, J26, J27: Conn_01x01_Pin; Pin_D1.2mm_pogo

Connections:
/GND: J9.2 (R), J10.1
/REF: J9.1 (T), J9.3 (T), J11.1
/in1+: J1.2 (R), J12.1
/in1-: J1.1 (T), J1.3 (T), J20.1
/in2+: J2.2 (R), J13.1
/in2-: J2.1 (T), J2.3 (T), J21.1
/in3+: J3.2 (R), J14.1
/in3-: J3.1 (T), J3.3 (T), J22.1
/in4+: J4.1 (T), J4.3 (T), J15.1
/in4-: J4.2 (R), J23.1
/in5+: J5.2 (R), J16.1
/in5-: J5.1 (T), J5.3 (T), J24.1
/in6+: J6.2 (R), J17.1
/in6-: J6.1 (T), J6.3 (T), J25.1
/in7+: J7.2 (R), J18.1
/in7-: J7.1 (T), J7.3 (T), J26.1
/in8+: J8.2 (R), J19.1
/in8-: J8.1 (T), J8.3 (T), J27.1

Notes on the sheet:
Module pads/pogo
Biosignal connectors
REf. connectors

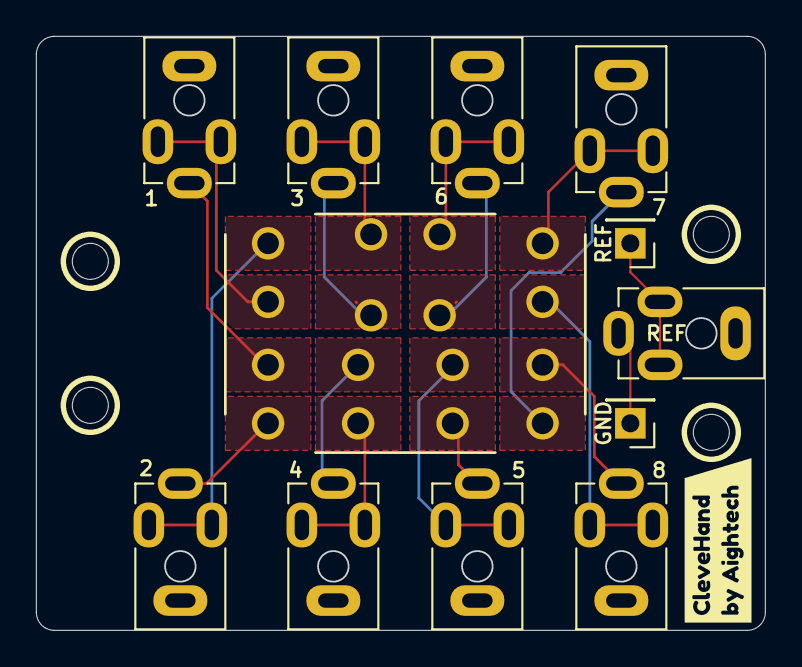
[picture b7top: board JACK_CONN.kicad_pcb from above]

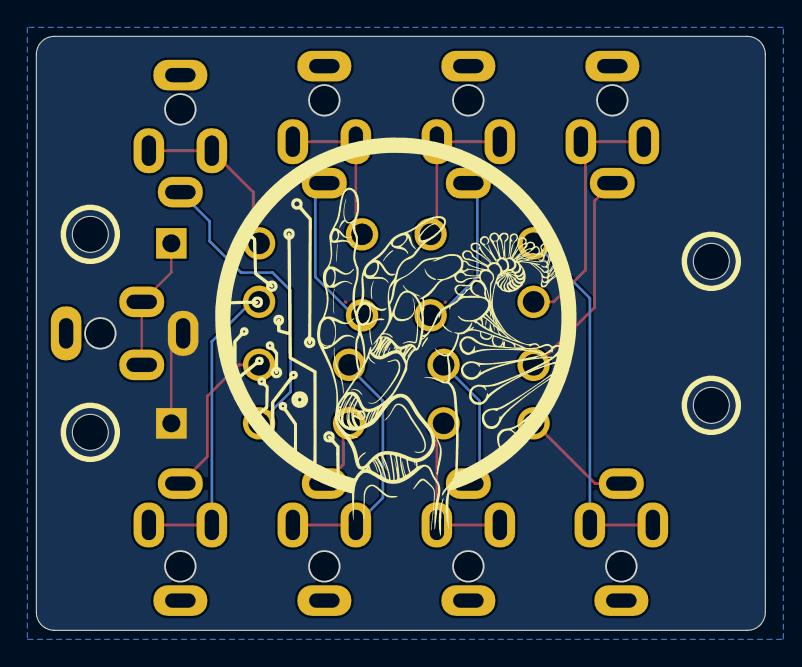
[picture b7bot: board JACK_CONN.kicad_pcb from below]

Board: 4 copper layers, 40.5 x 33.0 mm, 28 parts (16 on the bottom side), 18 nets.

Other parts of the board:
kibuzzard-6607178A: G***; kibuzzard-6607178A
